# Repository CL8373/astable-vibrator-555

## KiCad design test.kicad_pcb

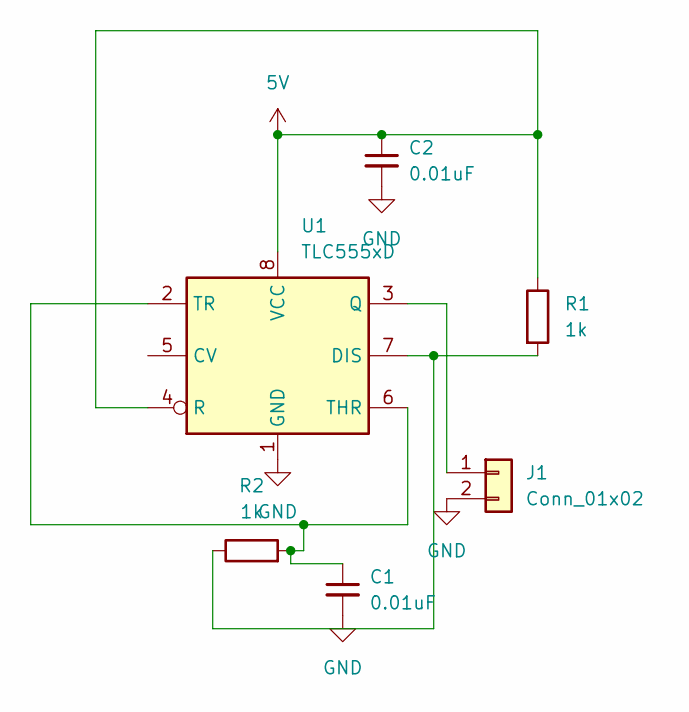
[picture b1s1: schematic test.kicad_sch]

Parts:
C1, C2: 0.01uF; C_1206_3216Metric_Pad1.33x1.80mm_HandSolder
J1: Conn_01x02; output connector
R1, R2: 1k; R_1206_3216Metric_Pad1.30x1.75mm_HandSolder
U1: TLC555xD; SOIC-8_3.9x4.9mm_P1.27mm

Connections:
5V: C2.1, R1.1, U1.4 (R), U1.8 (VCC)
GND: C1.2, C2.2, J1.2, U1.1 (GND)
unnamed: J1.1, U1.3 (Q)
unnamed: R1.2, R2.1, U1.7 (DIS)
unnamed: C1.1, R2.2, U1.2 (TR), U1.6 (THR)

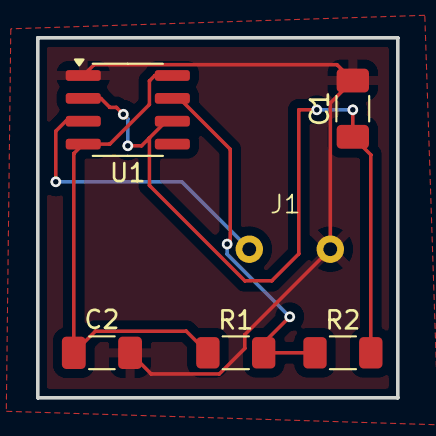
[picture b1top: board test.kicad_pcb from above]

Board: 2 copper layers, 20.0 x 20.0 mm, 6 parts (0 on the bottom side), 5 nets.

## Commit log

2024-10-24 astable vibrator 555 timer
